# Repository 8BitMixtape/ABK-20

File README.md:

# ABK-20

**8-Bit Algorithmic Audio Synthesizer with 5×4 NeoPixel Matrix Display**

The **ABK-20** is a modernized desktop hardware console redesign of the legendary **8Bit Mixtape**. Powered by a Microchip ATtiny85 running an 8-bit algorithmic sound engine (bytebeats, wavetable, granular, and punk console synths), it features an illuminated **20-LED (5×4) visual display screen**, tactile physical controls, and instant sound sketch loading via the **AudioBoot** bootloader.

---

## Hardware Highlights

* **Microcontroller**: Microchip ATtiny85 running at 16 MHz (Internal PLL).
* **Visual Display**: **20x WS2812B / SK6812 RGB NeoPixels** arranged in a 5-column × 4-row matrix for expressive animations, meters, and UI feedback.
* **Illuminated Slide Fader**: Bourns PTL20 20mm slide potentiometer with an integrated lever LED tied to the status/data line (`PB0`).
* **Tactile Controls**:
  * **Illuminated Rotary Potentiometer**: 10kΩ vertical potentiometer (`POT2-CV1` on `PB4`, RV09 / Alpha RD901F compatible) with illuminated transparent knurled shaft.
  * **Master Volume Control**: Side-mounted thumbwheel potentiometer (`POT3-Vol1`).
  * **Navigation Switch**: MTS-102 sub-miniature toggle switch (`SW3`) on `PB3` for menu navigation and mode selection.
  * **Illuminated User Button**: Highly KS01-BL-13 round illuminated push button (`SW2`) on the `PB3` resistor ladder.
  * **Hardware Reset Button**: Dedicated tactile push button (`SW4`) pulling `PB5` (Reset) to ground.
* **Audio Circuit**:
  * High-speed 8-bit PWM audio synthesized via Timer1 64 MHz PLL.
  * On-board PAM8002 audio amplifier optimized for unity gain ($R_{14} = 22\text{k}\Omega$, $C_5 = 1\mu\text{F}$, $C_8 = 100\text{nF}$) to prevent clipping and preserve deep sub-bass bytebeats through the internal speaker.
  * 3.5mm stereo output jack (switchable line-out / headphones with volume control).
* **AudioBoot Programming**: Upload new sound sketches directly through an audio cable or web browser—no external programmer or USB serial driver required.
* **Power Circuit**:
  * **USB-C 5V Input**: Modern 6-pin USB-C receptacle (`J5`) with dual 5.1kΩ pull-down resistors (`R17`, `R18` on CC1/CC2) for universal compatibility with USB-PD smart chargers and MacBook Type-C ports.
  * **Diode OR-ing Protection**: Automatic seamless power switching via Schottky diodes (`SS14`) across USB-C (5V), 7805 DC In (7–12V), and 3x AAA Battery input with reverse-charge protection.
  * **Master Power Switch**: Latching push switch (`SW1`) with power status LED (`D-POW1`). Cycling `SW1` provides the exact power-cycle timing required to activate AudioBoot sketch loading.

---

## Schematic

The ABK-20 schematic is organized into a modular **KiCad 9 hierarchical architecture**:

### Page 1: Main Architecture & Sound Engine
Controls, ATtiny85 microcontroller, audio filtering, power regulation, and hierarchical sub-sheet block.

### Page 2: 5×4 NeoPixel Display Matrix
Dedicated hierarchical sub-sheet (`hardware/LED_Matrix.kicad_sch`) with the raster-scan daisy-chained 20-LED array.

📄 **[Download Complete Multi-Page Schematic PDF (A4)](docs/hardware/ABK-20_schematic.pdf)**

---

## PCB Layout & 3D Model View

The compact **75×80 mm** rounded-corner desktop PCB design features the centered 5×4 NeoPixel display matrix, framed by the Bourns illuminated slide fader, clear-shaft illuminated rotary potentiometer, 3-way toggle switch, tactile buttons, thumbwheel volume pot, audio jacks, and side expansion headers:

### Hardware Variants & Comparison Showroom
The repository includes a dedicated standalone showroom board ([`ABK-20_showcase_variants.kicad_pcb`](hardware/ABK-20_showcase_variants.kicad_pcb)) for mechanical verification, 3D rendering, and rapid component swapping across various hardware options:
* **Audio Jacks**: PJ-317 vertical, PJ-342 SMD gullwing, and CUI SJ1-3525N horizontal jacks.
* **Faders & Pots**: 20mm and 30mm Bourns slide pots, Alpha RD901F vertical, and 16mm back-pad pots.
* **Power & Battery**: 3x AAA on-board battery clip holders, barrel jack, and USB-C.

### Component Staging & Exploration
Earlier component staging layout used during initial mechanical fit checks, 3D VRML model validation, and footprint library curation:

---

## Frontplate & Enclosure Ecosystem

The repository provides fully parametric OpenSCAD designs and production deliverables in [`production/`](production/):

### 1. Parametric 3D-Printed Frontplate (`production/ABK20-case/`)
A dedicated OpenSCAD front panel ([`ABK-20_frontplate_3dprint.scad`](production/ABK20-case/ABK-20_frontplate_3dprint.scad)) designed for standard 16 HP ($80.96 \times 92.28\text{ mm}$) Eurorack rails or the desktop laser-cut chassis:
* **Integrated 5×4 Baffle Grid**: Extends downward to the PCB to completely isolate each NeoPixel and prevent optical light bleed between cells.
* **Selectable Matrix Styles** (via OpenSCAD Customizer):
  * **`diffuser_grid`**: Integrated $0.20\text{ mm}$ translucent 3D-printed diffuser skin (single-extruder M600 filament swap: white on bed, colored panel face).
  * **`open_frame_grid`**: Crisp open apertures with elegant top edge bevels.
  * **`window_recess`**: Stepped frame recess for an acrylic window insert.
* **Mounting & Cutouts**: M3 Eurorack mounting slots with counterbore recesses, underside PCB corner standoffs, and precise cutouts for the slide fader, pots, switches, buttons, and expansion headers.
* **Pre-Rendered STL**: [`ABK-20_frontplate_3dprint.stl`](production/ABK20-case/ABK-20_frontplate_3dprint.stl) and configuration presets in [`ABK-20_frontplate_3dprint.json`](production/ABK20-case/ABK-20_frontplate_3dprint.json).

<p align="center">
  
  &nbsp;&nbsp;&nbsp;&nbsp;
  
</p>

### 2. Laser-Cut Frontplates (`production/frontplate/`)
* **Vector Artwork Panels** ([`production/frontplate/ABK_frontplate_02.svg`](production/frontplate/ABK_frontplate_02.svg), [`output.pdf`](production/frontplate/output.pdf)): High-detail laser cutting and surface engraving artwork with silkscreen labeling and control indicators.

### 3. Parametric Enclosures (`production/ABK20-case/`)
* **3D-Printable Snap-Fit Enclosure** ([`ABK-20_case_3dprint.scad`](production/ABK20-case/ABK-20_case_3dprint.scad), [`.stl`](production/ABK20-case/ABK-20_case_3dprint.stl), [`.3mf`](production/ABK20-case/ABK-20_case_3dprint.3mf)):
  * Two-part direct-fit enclosure (`top_shell` + `bottom_cover`) designed for supportless FDM 3D printing with integrated 5×4 NeoPixel baffle grid.
  * **Prototype Hardware Support (Preset: `"perfect Proto"`)**: Specifically tailored for early prototype boards with top-mounted PJ-317 audio jacks. Adds beveled rectangular window cutouts ($14.5\times 15.5\text{ mm}$, $R=1.4\text{ mm}$) centered over each jack and widens lateral board clearance to $1.5\text{ mm}$ for effortless PCB insertion around the side thumbwheel volume pot.
  * **Standard Production (Preset: `"ABK-20_diffuser_grid"`)**: Solid continuous top face with rear-exiting audio jack ports.
* **Laser-Cut Desktop Console ("Chistli")** ([`ABK-20_case.scad`](production/ABK20-case/ABK-20_case.scad)):
  * Parametric finger-jointed desktop chassis in 3mm acrylic or wood with an ergonomic $12^\circ$ playing tilt.
  * Extended side cheeks with custom corner radii and Eurorack rail mounting options.
* **Enclosure Documentation**: [**`production/ABK20-case/README.md`**](production/ABK20-case/README.md) & [**`CASE_DESIGN_NOTES.md`**](production/ABK20-case/CASE_DESIGN_NOTES.md).

<p align="center">
  
  &nbsp;&nbsp;&nbsp;&nbsp;
  
</p>

### 4. Acoustic Optimization & Waveguide Engineering
The repository includes a comprehensive acoustic engineering architecture to solve the acoustic dipole short-circuit on rear-mounted micro-speakers and dramatically enhance bass/mid punch on physical hardware:
* **Master Engineering Plan**: [**`production/ABK20-case/ACOUSTIC_OPTIMIZATION_PLAN.md`**](production/ABK20-case/ACOUSTIC_OPTIMIZATION_PLAN.md)
  * **Downward Acoustic Chimney Waveguide**: Integrated directly into both the 3D-printed case ceiling and Eurorack faceplate. Tapers downward to seal against the PCB acoustic holes, transforming the $8.1\text{ mm}$ airspace into an acoustic horn with $+3\text{ to }+6\text{ dB}$ higher acoustic projection and zero internal sound spill.
  * **8 Classic Vintage Sound Grill Styles** (selectable via `speaker_grill_style`):
    * **`horiz_slots`**: Classic Dieter Rams / Braun T3 tiered horizontal slits.
    * **`horiz_4slots`**: 4 thin horizontal slits (retro 70s/80s Hi-Fi cassette deck).
    * **`soundwave`**: 7 graduated vertical slits forming an analog synth graphic EQ waveform.
    * **`braun_dots`**: 19-hole staggered precision dot matrix (Braun ET66 / T41).
    * **`chevron`**: $45^\circ$ angled Japanese synth louvers (Roland TR/TB style).
    * **`radial`**: 1950s transistor radio radial dial spoke starburst.
    * **`slots`**: Classic 5 vertical Eurorack slots.
    * **`aperture`**: Open framed window for real speaker cloth or brass wire mesh.
  * **Modular Acoustic Kit** ([`production/ABK20-case/ABK-20_speaker_acoustic_kit.scad`](production/ABK20-case/ABK-20_speaker_acoustic_kit.scad)):
    * Parametric sealed and Helmholtz bass-reflex back-box cups (Standard $2.4\text{ cm}^3$, XL $5.1\text{ cm}^3$, and MAX $6.3\text{ cm}^3$) with extended snorkel ducts tuned to $280-360\text{ Hz}$.
    * **Support-Free Printing**: Continuous flat PCB support keel at $Z = \text{depth}$ with $\le 45^\circ$ transitional chamfers prints 100% support-free when oriented flange-down.
  * **Precision Centering**: Added `panel_alignment = "symmetric"` to resolve legacy SVG viewBox offsets, achieving exact $2.98\text{ mm}$ symmetrical PCB margins and balanced top jack outer walls.

---

## ATtiny85 Pin Mapping

| Pin | Physical | Port | Macro | Function / Description |
| :---: | :---: | :---: | :---: | :--- |
| **PB0** | Pin 5 | `PB0` | `NEOPIXELPIN` | 800 kHz data stream to 5×4 NeoPixel Matrix (via R9 330Ω) & Fader Lever LED (`RV1B`) |
| **PB1** | Pin 6 | `PB1` | `SPEAKERPIN` | High-speed PWM audio output (Timer1 64 MHz PLL) to Volume Pot & PAM8002 amp |
| **PB2** | Pin 7 | `PB2` | `POTI_LEFT` | Slide Potentiometer (`RV1A`) analog control input (ADC1) |
| **PB3** | Pin 2 | `PB3` | `BUTTON_PIN` | AudioBoot audio input (AC-coupled 100nF) & multi-state button resistor ladder (ADC3) |
| **PB4** | Pin 3 | `PB4` | `POTI_RIGHT` | 10kΩ Rotary Potentiometer (`POT2-CV1`) analog control input (ADC2) |
| **PB5** | Pin 1 | `PB5` | `RESET_PIN` | Hardware Reset button (`SW4`) & Sync jumper (`J6`). *(Can be converted to MIDI IN with `RSTDISBL`)* |

---

## Firmware & Web Flasher

* **[ABK-20 Online Web Audio Player & Flasher](https://8bitmixtape.github.io/ABK-20/)** (hosted directly from [`web/index.html`](web/index.html))
* **[Software & Sketches Suite](software/)** (PlatformIO build environment, `hex2wav` pipeline, and 30+ sound sketches)
* Also compatible with the [8Bit-Vintage Firmware Repository](https://github.com/8BitMixtape/8Bit-Vintage)

---

## TinyAudioBoot Bootloader (ABK-20 Custom Edition)

The ABK-20 features a dedicated, highly optimized build of **TinyAudioBoot** for ATtiny85 running at 16 MHz internal PLL, fully documented in [**`software/tools/bootloader/`**](software/tools/bootloader/):

* **Skipper Edition** ([`TinyAudioBoot_Skipper_ABK-20.hex`](software/tools/bootloader/hex/TinyAudioBoot_Skipper_ABK-20.hex), 960 bytes):
  * **Instant Boot**: Starts the active synthesizer sketch in $< 25\text{ ms}$ upon normal power-on.
  * **Upload Mode on Demand**: Enters a 30-second audio upload window *only* when holding button **`SW2`** during power-up or reset.
* **Standard Edition** ([`TinyAudioBoot_Standard_ABK-20.hex`](software/tools/bootloader/hex/TinyAudioBoot_Standard_ABK-20.hex), 874 bytes):
  * Provides an automatic 5-second audio upload window on every power cycle.
* **Silent Standby on PB1**:
  * Actively clamps `PB1` to GND during bootloader standby so there are zero pops, clicks, or 1 Hz ticking chirps in headphones or speaker.
* **Page-Write Bi-Color Visuals**:
  * Alternates **Green $\leftrightarrow$ Red** on every 64-byte flash page write for real-time visual progress monitoring.
* **Flash Budget**:
  * Occupies $\le 1\text{ KB}$ at address `0x1C00`, maximizing flash memory to **7,168 bytes** ($0\text{x0000} \to 0\text{x1BFF}$) for user sketches.
* **ISP Flashing & Fuses**:
  * Quick one-liner AVRDUDE flash commands and fuse reference (`lfuse: 0xe1`, `hfuse: 0xdd`, `efuse: 0xfe`) are detailed in [**`software/tools/bootloader/burn_bootloader.md`**](software/tools/bootloader/burn_bootloader.md).
* **Architecture & Evolution**:
  * Comprehensive breakdown of all circuit and firmware differences compared to the original v3.0–v3.2 bootloader in [**`software/tools/bootloader/BOOTLOADER_EVOLUTION_AND_DIFFERENCES.md`**](software/tools/bootloader/BOOTLOADER_EVOLUTION_AND_DIFFERENCES.md).

---

## Repository Structure

```
ABK-20/
├── .agents/                          # Antigravity agent rules & 8Bit Mixtape skills
├── web/                              # Web AudioBoot player & sound app catalog (GitHub Pages)
│   ├── index.html                    # Online Web Audio Flasher & synthesizer player
│   ├── apps.json & apps.js           # Sound track catalog metadata & registry
│   ├── wav/                          # Production 8-bit bootloader audio streams (.wav)
│   ├── audio/                        # 30-second audio preview MP3s
│   ├── gifs/                         # Animated 5x4 matrix LED previews (solid clean mode)
│   └── manuals/                      # Individual user manuals for each sound application
├── docs/                             # Project documentation, hardware notes & datasheets
│   ├── hardware/                     # Circuit notes, engineering summaries & schematics
│   │   ├── HARDWARE_NOTES.md         # Hardware & circuit design notes
│   │   ├── REV03_ENGINEERING_SUMMARY.md # Engineering breakdown
│   │   ├── AMP_AUTO_SHUTDOWN_CIRCUIT.md # LM4871 amp shutoff specification
│   │   ├── DESIGN_VARIANTS_GUIDE.md  # Alternative layout variants
│   │   └── ABK-20_schematic.pdf      # Multi-page A4 schematic export
│   ├── datasheets/                   # Component datasheets (Bourns faders, switches, pots)
│   ├── fabrication/                  # DIY etching & drilling guides (ABK-20_DIY_DRILL_HANDOUT.pdf)
│   ├── history/                      # 8Bit Mixtape lineage & Coconut doctrine (HISTORY_AND_ARCHITECTURE.md)
│   ├── software/                     # Software developer guides (WORKFLOW_GIF_GENERATION.md)
│   └── img/                          # Images, 3D renders & diagrams
├── hardware/                         # KiCad 8 EDA design source files
│   ├── ABK-20.kicad_pro              # Factory Project: KiCad project file
│   ├── ABK-20.kicad_sch              # Factory Project: Main hierarchical schematic (Page 1)
│   ├── ABK-20.kicad_pcb              # Factory Project: Board layout (JLCPCB / PTH / SMT)
│   ├── ABK-20_DIY.kicad_pro          # DIY Project: KiCad project file
│   ├── ABK-20_DIY.kicad_sch          # DIY Project: Dedicated schematic (Page 1)
│   ├── ABK-20_DIY.kicad_pcb          # DIY Project: Board layout (non-PTH / wire-vias / pilot marks)
│   ├── ABK-20_showcase_variants.*    # Standalone showroom project with alternative footprints
│   ├── LED_Matrix.kicad_sch          # 5x4 NeoPixel matrix sub-sheet (Page 2)
│   ├── mixtape_schematics.kicad_sym  # Project symbol library
│   ├── 8Bitmixtape_reworked.pretty/  # Project footprint library
│   ├── 3d_models/                    # Self-contained bundled 3D models
│   ├── bom/                          # Hardware schematic BOM exports
│   └── scripts/                      # Layout, 3D WRL & thumbnail scripts
├── production/                       # Physical manufacturing & fabrication deliverables
│   ├── bom/                          # Interactive HTML Bill of Materials (iBOM)
│   ├── gerbers/                      # Standard fabrication drill & Gerber archives
│   ├── MASK/                         # High-res vector masks for DIY PCB chemical etching
│   ├── frontplate/                   # Laser-cut / CNC front panel vector drawings (SVG)
│   └── ABK20-case/                   # 3D printable enclosures and mechanical drawings
└── software/                         # Embedded C++ firmware, tools & asset pipelines
    ├── platformio.ini                # PlatformIO ATtiny85 @ 16 MHz build configuration
    ├── src/                          # 30+ algorithmic sound sketches (.cpp)
    ├── include/                      # Hardware pinouts & shared sound engine headers (.h)
    ├── scripts/                      # Asset pipelines (build_wavs, gen_previews, gen_audio_previews)
    └── tools/
        ├── bootloader/               # TinyAudioBoot sources, Makefile & precompiled HEX binaries
        └── hex2wav/                  # Standalone Hex-to-Audio bootloader converter
```

---

## License

Licensed under the **[CERN Open Hardware Licence Version 2 – Strongly Reciprocal](LICENSE)** (CERN-OHL-S-2.0).

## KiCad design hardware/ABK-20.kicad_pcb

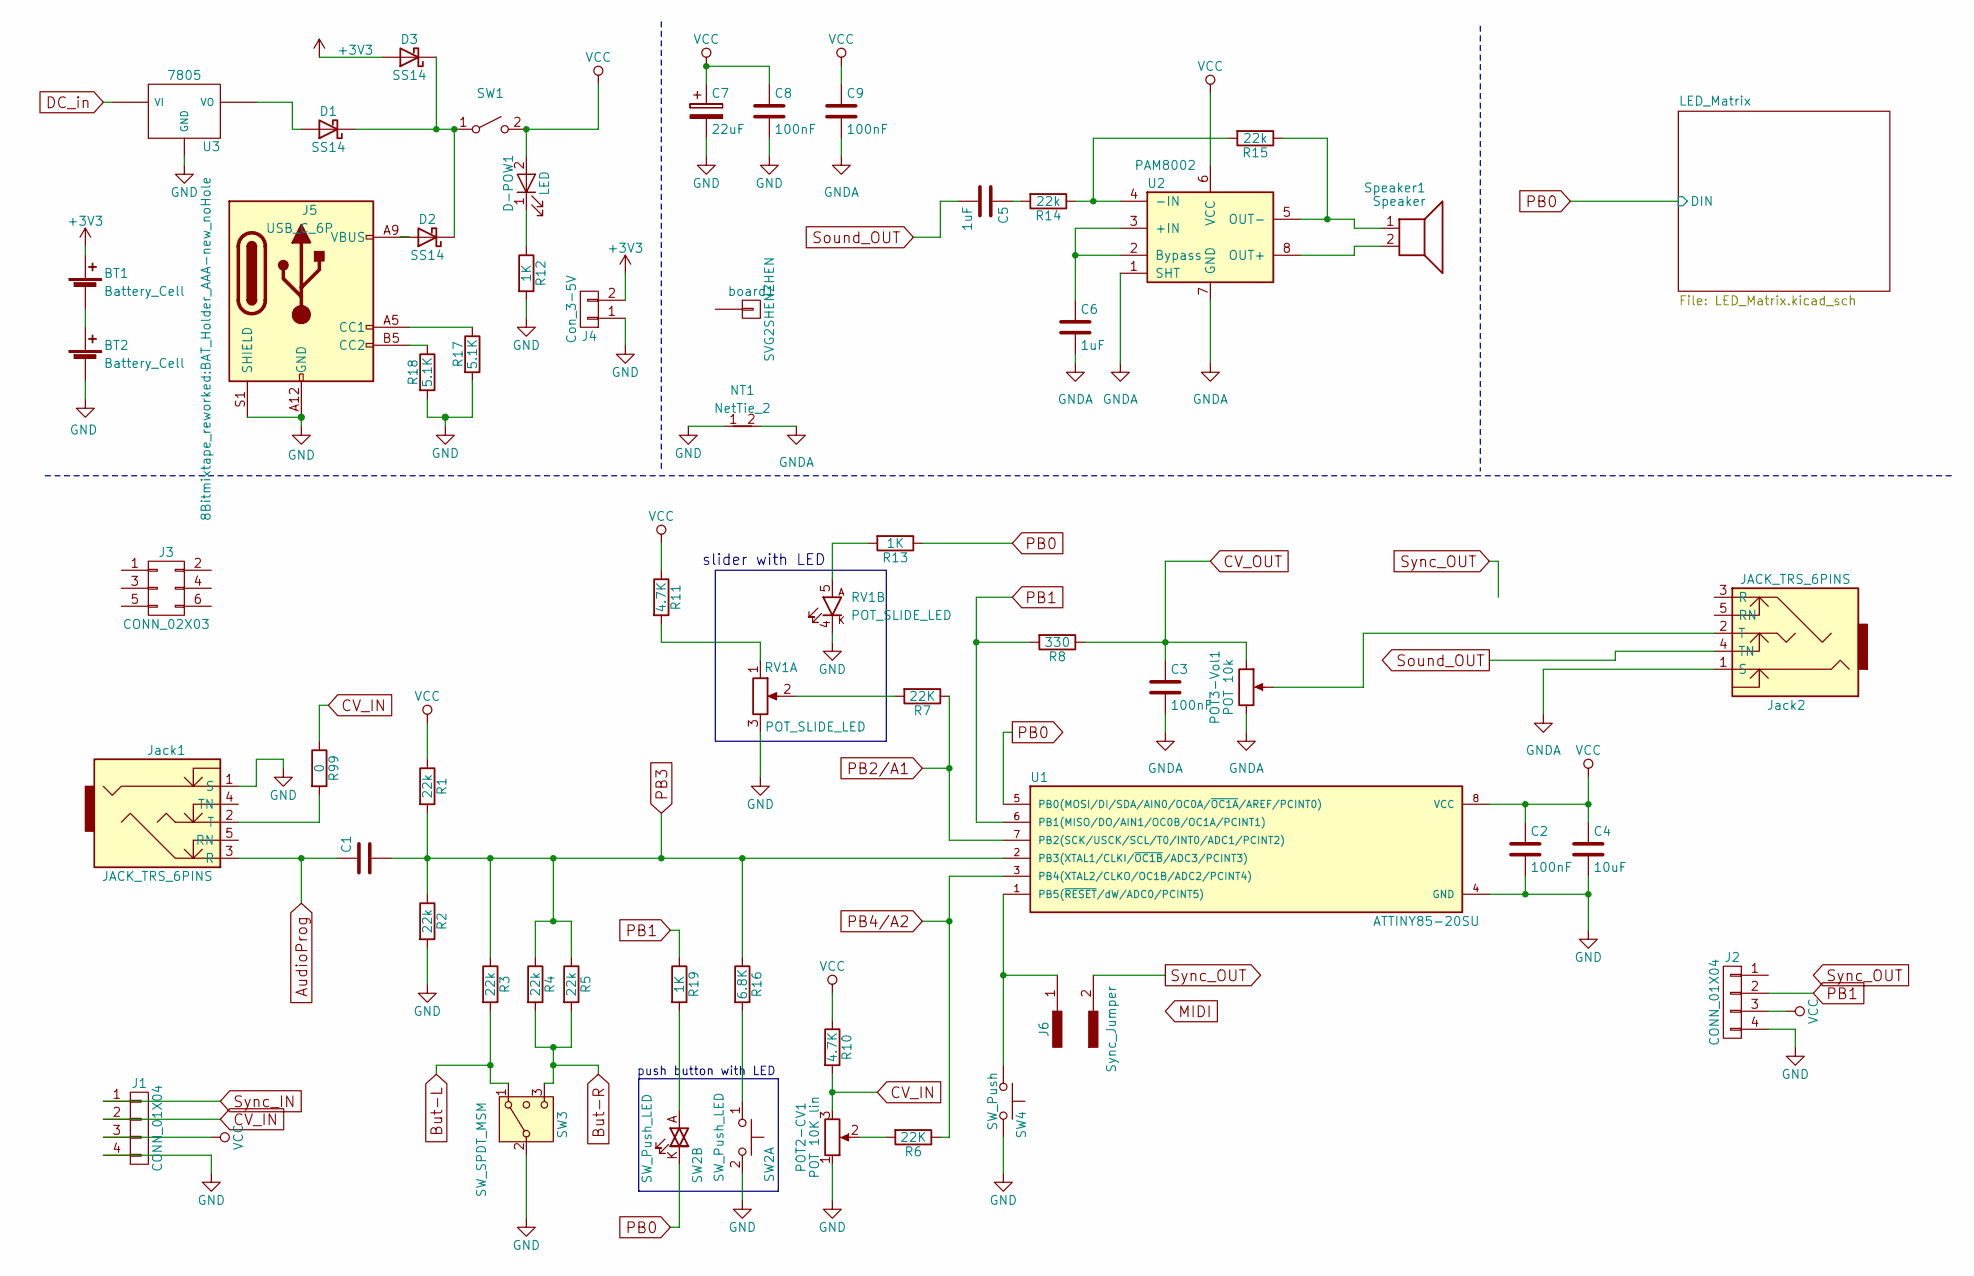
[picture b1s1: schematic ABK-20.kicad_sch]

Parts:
BT1, BT2: Battery_Cell; BAT_Holder_AAA-new_noHole
C1, C2, C3, C8, C9: 100nF; C_1210_noGND
C4: 10uF; C_1210_noGND
C5, C6: 1uF; C_1210_noGND
C7: 22uF; C_1210_noGND
D1, D2, D3: SS14; D_SMA
D-POW1: LED; LED_2835_minimal
J1: CONN_01X04; Angled_1x04_Pitch2.54mm-flip
J2: CONN_01X04; PinSocket_1x04_P2.54mm_Vertical
J3: CONN_02X03; Socket_Strip_Straight_2x03_Pitch2.54mm
J4: Con_3-5V; Bat_connector_SMD
J5: USB_C_6P; USB_C_6Pin_PowerOnly
J6: Sync_Jumper; Sync_jumper_small
Jack1, Jack2: JACK_TRS_6PINS; AUDIO-Jack_3.5mm_PJ-317
NT1: NetTie_2; NetTie-2_SMD_Pad2.0mm
POT2-CV1: POT 10K lin; Potentiometer_RV09_Vertical_ClearShaft
POT3-Vol1: POT 10k; Potentiometer_wheel
R1, R2, R3, R4, R5, R14, R15: 22k; R_1206_noGND_sm
R6, R7: 22K; R_1206_noGND_sm
R8: 330; R_1206_noGND_sm
R10, R11: 4.7K; R_1206_noGND_sm
R12, R13, R19: 1K; R_1206_noGND_sm
R16: 6.8K; R_1206_noGND_sm
R17, R18: 5.1K; R_1206_noGND_sm
R99: 0; R_1206_noGND_sm
RV1: POT_SLIDE_LED; Potentiometer_Bourns_PTL20_Single_Slide_LED
SW1: SW_SPST; Push_SWITCH_hole
SW2: SW_Push_LED; SW_Push_Highly_KS01-BL-13
SW3: SW_SPDT_MSM; SW_Toggle_SPDT_SubMini_SMTS-103
SW4: SW_Push; SW_SPST_FSMSM
Speaker1: Speaker; SpeakerPads_SMD
U1: ATTINY85-20SU; Attiny_DIP-8_W7.62mm_mod
U2: PAM8002; SO-8_fixed
U3: 7805; TO-252-3_TabPin2
board1: SVG2SHENZHEN; Mixtape_reworked

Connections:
+3V3: BT1.1 (+), D3.2 (A), J4.2
AudioProg: C1.1, Jack1.3 (R)
But-L: R3.2, SW3.1
But-R: R4.2, R5.2, SW3.3 (4)
CV_IN: J1.2, POT2-CV1.3, R10.2, R99.1
CV_OUT: C3.1, POT3-Vol1.1, R8.1
DC_in: U3.1 (VI)
GND: BT2.2 (-), C2.2, C4.2, C7.2, C8.2, J1.4, J2.4, J4.1, J5.A12 (GND), J5.B12 (GND), J5.S1 (SHIELD), Jack1.1 (S), NT1.1, POT2-CV1.1, R2.2, R12.2, R17.2, R18.2, RV1.3, RV1.4 (K), SW2.2, SW3.2 (3), SW4.2, U1.4 (GND), U3.2 (GND); also elsewhere on the board
GNDA: C3.2, C6.2, C9.2, Jack2.1 (S), NT1.2, POT3-Vol1.3, U2.1 (SHT), U2.7 (GND)
unnamed: BT1.2 (-), BT2.1 (+)
unnamed: C5.1, R14.2
unnamed: D1.2 (A), U3.3 (VO)
unnamed: D1.1 (K), D2.1 (K), D3.1 (K), SW1.1 (A)
unnamed: D2.2 (A), J5.A9 (VBUS), J5.B9 (VBUS)
unnamed: D-POW1.1 (K), R12.1
unnamed: J5.A5 (CC1), R17.1
unnamed: J5.B5 (CC2), R18.1
unnamed: Jack1.2 (T), R99.2
unnamed: Jack2.2 (T), POT3-Vol1.2
unnamed: POT2-CV1.2, R6.2
unnamed: R7.2, RV1.2
unnamed: R11.2, RV1.1
unnamed: R16.2, SW2.1
unnamed: R19.2, SW2.A
unnamed: R13.2, RV1.5 (A)
unnamed: J6.1, SW4.1, U1.1 (PB5(~RESET/dW/ADC0/PCINT5))
unnamed: C6.1, U2.2 (Bypass), U2.3 (+IN)
unnamed: R14.1, R15.2, U2.4 (-IN)
unnamed: Speaker1.2, U2.8 (OUT+)
unnamed: R15.1, Speaker1.1, U2.5 (OUT-)
PB0: R13.1, SW2.K, U1.5 (PB0(MOSI/DI/SDA/AIN0/OC0A/~OC1A/AREF/PC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); also elsewhere on the board
PB1: J2.2, R8.2, R19.1, U1.6 (PB1(MISO/DO/AIN1/OC0B/OC1A/PCINT1))
PB2/A1: R7.1, U1.7 (PB2(SCK/USCK/SCL/T0/INT0/ADC1/PCINT2))
PB3: C1.2, R1.2, R2.1, R3.1, R4.1, R5.1, R16.1, U1.2 (PB3(XTAL1/CLKI/~OC1B/ADC3/PCINT3))
PB4/A2: R6.1, U1.3 (PB4(XTAL2/CLKO/OC1B/ADC2/PCINT4))
Sound_OUT: C5.2, Jack2.4 (TN)
Sync_IN: J1.1
Sync_OUT: J6.2
VCC: C2.1, C4.1, C7.1, C8.1, C9.1, D-POW1.2 (A), J1.3, J2.3, R1.1, R10.1, R11.1, SW1.2 (B), U1.8 (VCC), U2.6 (VCC); also elsewhere on the board

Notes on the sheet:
slider with LED
push button with LED

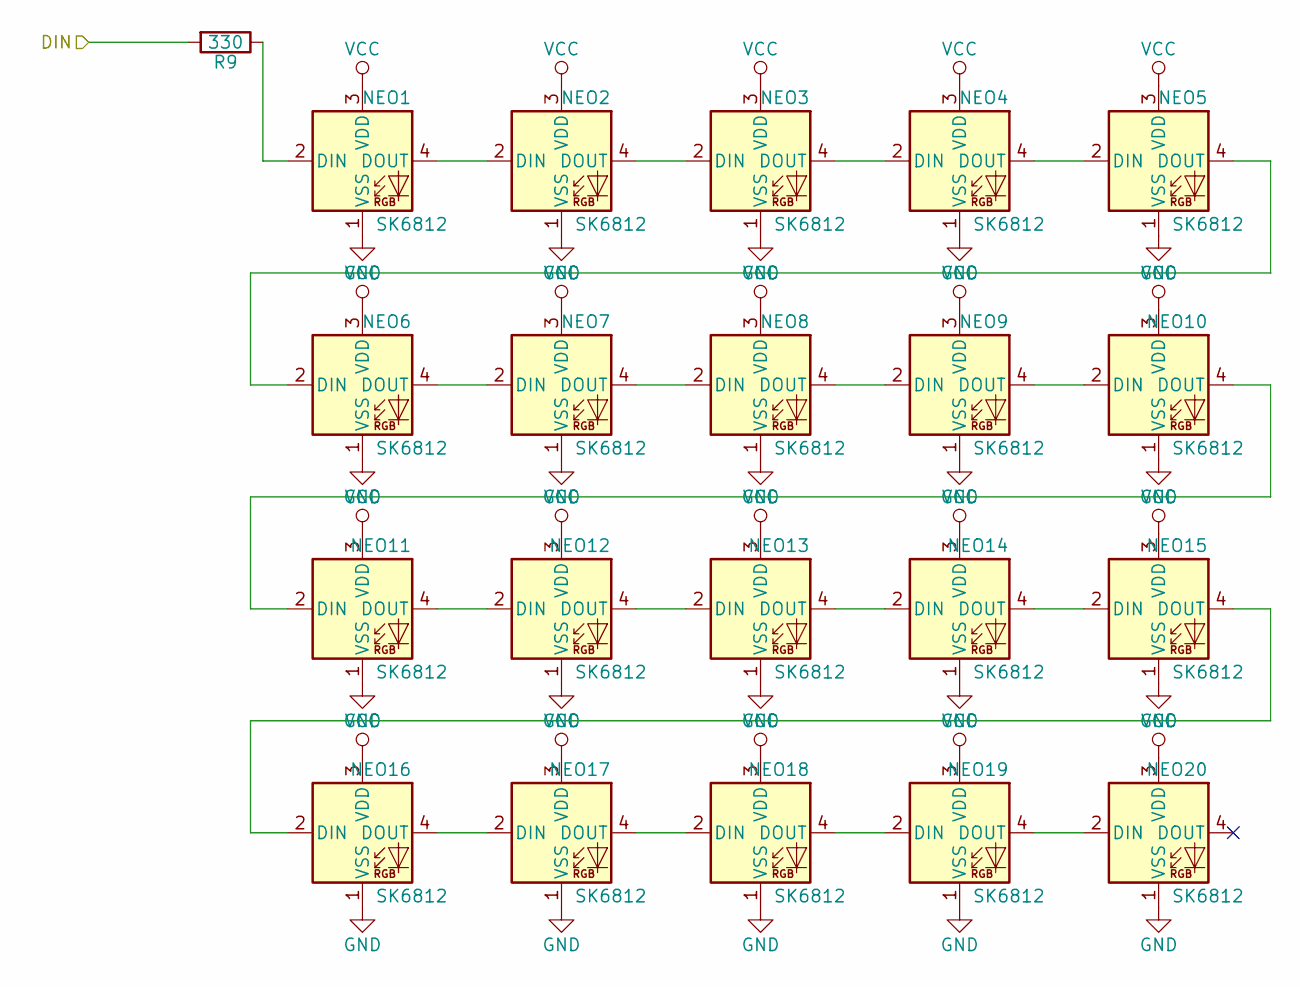
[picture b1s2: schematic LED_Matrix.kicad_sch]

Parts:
NEO1, NEO2, NEO3, NEO4, NEO5, NEO6, NEO7, NEO8, NEO9, NEO10, NEO11, NEO12, NEO13, NEO14, NEO15, NEO16, NEO17, NEO18, NEO19, NEO20: SK6812; Mixtape_NEO_WS2812B
R9: 330; R_1206_noGND_sm

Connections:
GND: NEO1.1 (VSS), NEO2.1 (VSS), NEO3.1 (VSS), NEO4.1 (VSS), NEO5.1 (VSS), NEO6.1 (VSS), NEO7.1 (VSS), NEO8.1 (VSS), NEO9.1 (VSS), NEO10.1 (VSS), NEO11.1 (VSS), NEO12.1 (VSS), NEO13.1 (VSS), NEO14.1 (VSS), NEO15.1 (VSS), NEO16.1 (VSS), NEO17.1 (VSS), NEO18.1 (VSS), NEO19.1 (VSS), NEO20.1 (VSS); also elsewhere on the board
unnamed: NEO1.2 (DIN), R9.1
unnamed: NEO1.4 (DOUT), NEO2.2 (DIN)
unnamed: NEO2.4 (DOUT), NEO3.2 (DIN)
unnamed: NEO3.4 (DOUT), NEO4.2 (DIN)
unnamed: NEO4.4 (DOUT), NEO5.2 (DIN)
unnamed: NEO5.4 (DOUT), NEO6.2 (DIN)
unnamed: NEO6.4 (DOUT), NEO7.2 (DIN)
unnamed: NEO7.4 (DOUT), NEO8.2 (DIN)
unnamed: NEO8.4 (DOUT), NEO9.2 (DIN)
unnamed: NEO9.4 (DOUT), NEO10.2 (DIN)
unnamed: NEO10.4 (DOUT), NEO11.2 (DIN)
unnamed: NEO11.4 (DOUT), NEO12.2 (DIN)
unnamed: NEO12.4 (DOUT), NEO13.2 (DIN)
unnamed: NEO13.4 (DOUT), NEO14.2 (DIN)
unnamed: NEO14.4 (DOUT), NEO15.2 (DIN)
unnamed: NEO15.4 (DOUT), NEO16.2 (DIN)
unnamed: NEO16.4 (DOUT), NEO17.2 (DIN)
unnamed: NEO17.4 (DOUT), NEO18.2 (DIN)
unnamed: NEO18.4 (DOUT), NEO19.2 (DIN)
unnamed: NEO19.4 (DOUT), NEO20.2 (DIN)
PB0: R9.2; also elsewhere on the board
VCC: NEO1.3 (VDD), NEO2.3 (VDD), NEO3.3 (VDD), NEO4.3 (VDD), NEO5.3 (VDD), NEO6.3 (VDD), NEO7.3 (VDD), NEO8.3 (VDD), NEO9.3 (VDD), NEO10.3 (VDD), NEO11.3 (VDD), NEO12.3 (VDD), NEO13.3 (VDD), NEO14.3 (VDD), NEO15.3 (VDD), NEO16.3 (VDD), NEO17.3 (VDD), NEO18.3 (VDD), NEO19.3 (VDD), NEO20.3 (VDD); also elsewhere on the board

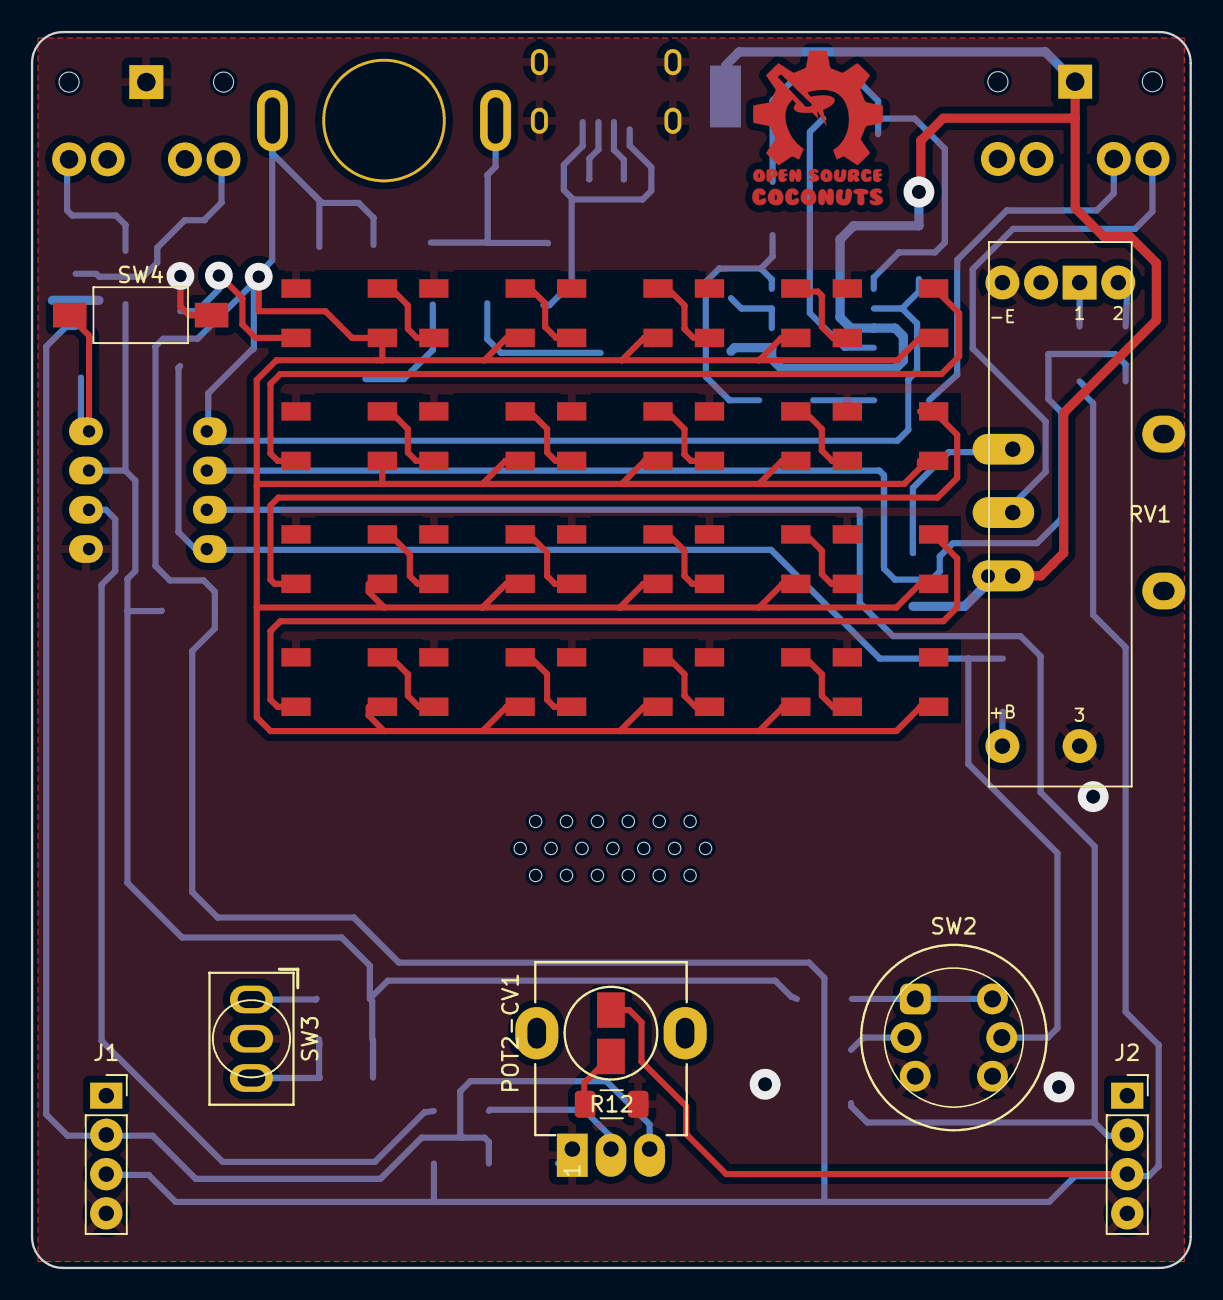
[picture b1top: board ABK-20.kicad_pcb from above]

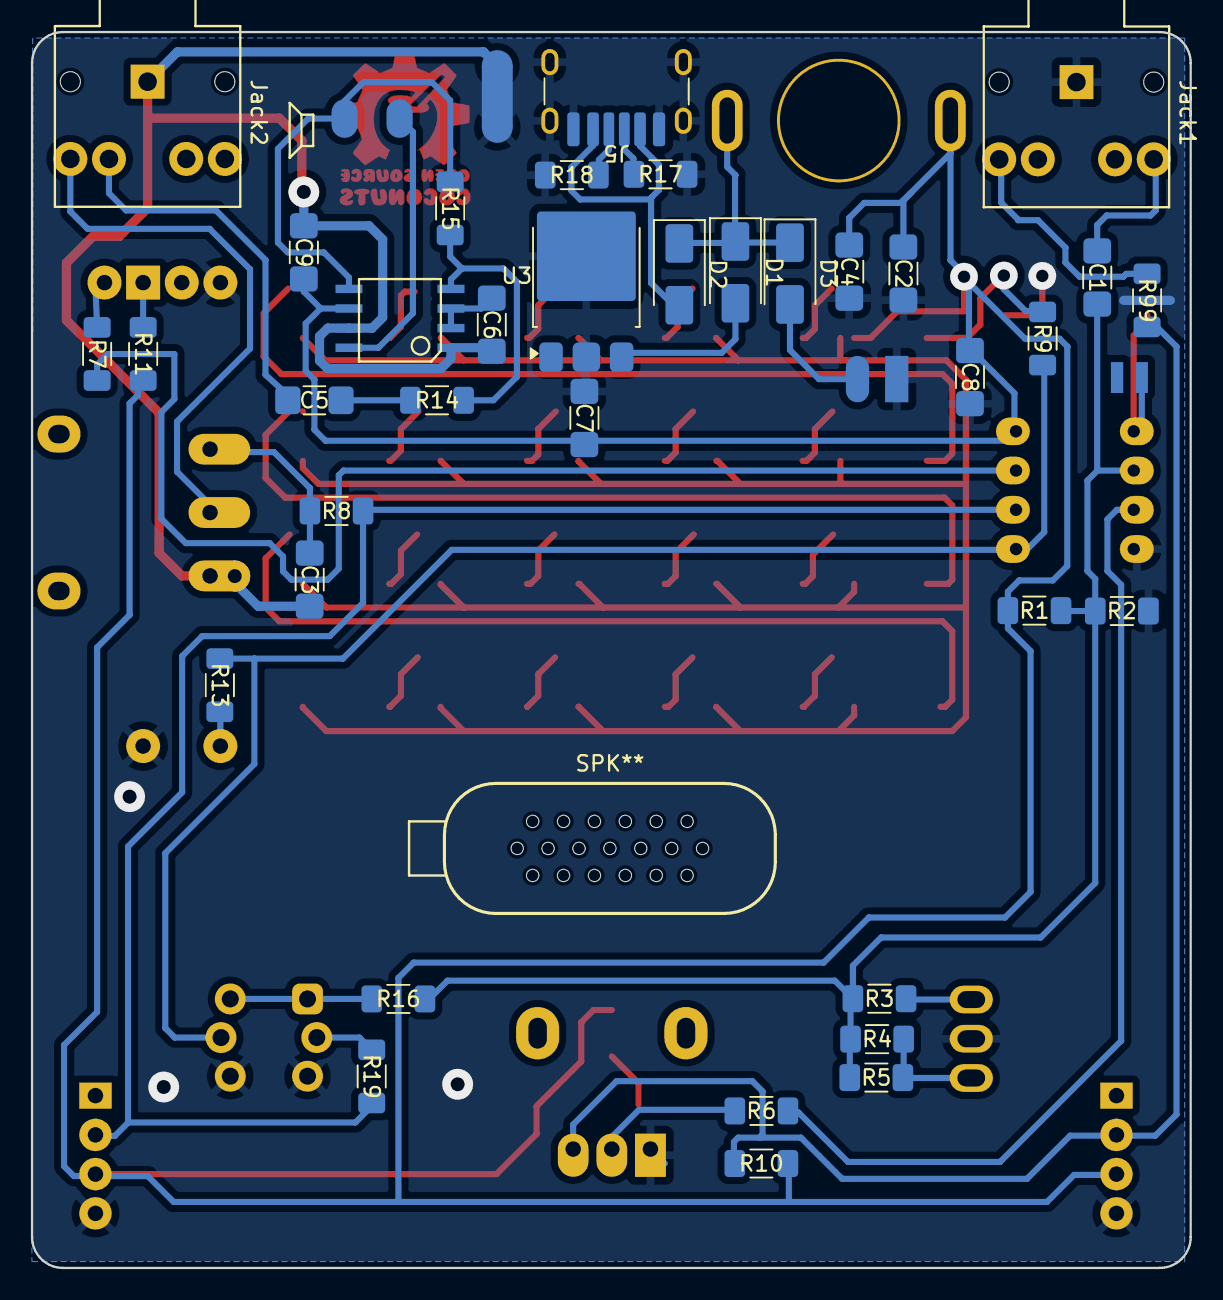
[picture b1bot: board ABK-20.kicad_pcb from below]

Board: 2 copper layers, 75.0 x 80.0 mm, 74 parts (42 on the bottom side), 55 nets.

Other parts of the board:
Ref**: Val**; Coconut_logo_sm
SPK**: Speaker_Micro_Loch_Honeycomb

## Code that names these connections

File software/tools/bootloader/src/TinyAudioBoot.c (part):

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  v3.1  04.2.2017 C. -H-A-B-E-R-E-R-  clean reset vector added, description added, pins rerouted
  v3.2  18.7.2017 C. -P-r-a-k-o-s-a-  various refactor, added eeprom write mode, makefile for compiling using arduino ide toolchain
  v3.3  25.10.2026 M. -D-U-S-S-E-I-L-L-E-R- (dusjagr) & Antigravity
                   - Silent speaker standby: PB1 held at GND (0V) while PB0 blinks Red @ 1 Hz
                   - Alternating Green <-> Red bi-color LED visual feedback on each 64-byte page
                   - Code size optimizations (pgm_read_word, inline delay loops) down to 872 bytes
                   - Standard 1KB boundary at 0x1C00 (leaves 7,168 bytes flash for user sketches)
                   - Configurable upload timeout: 5s for Standard, 30s for Skipper
  v4.0  25.10.2026 M. -D-U-S-S-E-I-L-L-E-R- (dusjagr) & Antigravity - ABK-20 Skipper Edition
                   - Instant boot: skips bootloader in <25ms unless button SW2 is held on power-up
                   - PB3 analog resistor ladder ADC decoder (calibrated threshold ADCH <= 60 / < 1.18V)
                   - ADC-based button release wait and 20ms debounce (prevents chatter lockups)
                   - Unified single-source architecture controlled via -DUSE_SKIPPER (958 bytes)

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				
	   			     _______
                                    |   U   |
         (PCINT5/RESET/ADC0/dW) PB5-|       |- VCC
  (PCINT3/XTAL1/CLKI/OC1B/ADC3) PB3-| ATTINY|- PB2 (SCK/USCK/SCL/ADC1/T0/INT0/PCINT2) 
  (PCINT4/XTAL2/CLKO/OC1B/ADC2) PB4-|   85  |- PB1 (MISO/DO/AIN1/OC0B/OC1A/PCINT1) 
                                GND-|       |- PB0 (MOSI/DI/SDA/AIN0/OC0A/OC1A/AREF/PCINT0)	 
                                    |_______|

				  
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				  ==============
                                     _______				  
                                    |   U   |				  
                          reset/PB5-|       |- VCC				  
                 D3/A3          PB3-| ATTINY|- PB2       D2/A1				  
    soundprog->  D4/A2          PB4-|   85  |- PB1       D1     -> ARDUINO_LED
                                GND-|       |- PB0       D0
                                    |_______|		


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
#ifdef DEBUGON

	#define DEBUGPIN       ( 1<<PB2 ) 
	#define INITDEBUGPIN   { DDRB  |=  DEBUGPIN; }

	#define DEBUGPINON     { PORTB |=  DEBUGPIN;}
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#ifdef USELED

#define INITLED do { \
    DDRB |= (1 << PB0) | (1 << PB1); \
    PORTB &= ~((1 << PB0) | (1 << PB1)); \
} while(0)

#define LED_GREEN()    do { PORTB = (PORTB & ~(1 << PB0)) | (1 << PB1); } while(0)
#define LED_RED()      do { PORTB = (PORTB & ~(1 << PB1)) | (1 << PB0); } while(0)
#define LED_OFF()      do { PORTB &= ~((1 << PB0) | (1 << PB1)); } while(0)
#define TOGGLE_GREEN() do { PORTB &= ~(1 << PB0); PORTB ^= (1 << PB1); } while(0)
#define TOGGLE_RED()   do { PORTB &= ~(1 << PB1); PORTB ^= (1 << PB0); } while(0)

#define LEDON      LED_RED()
#define LEDOFF     LED_OFF()
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
#endif

#define INPUTAUDIOPIN (1<<PB3) //
#define PINVALUE (PINB&INPUTAUDIOPIN)
#define INITAUDIOPORT {DDRB&=~INPUTAUDIOPIN;} // audio pin is input

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}

#ifdef USE_SKIPPER
// Skipper button check on PB3 analog ladder
static inline void checkBootloaderSkip(void)
{
  // Power settling delay (~20ms @ 16MHz) for VCC rail and 100nF C1 capacitor
  _delay_ms(20);

  // ADC3 on PB3, VCC reference, Left-adjust result (8-bit reading in ADCH)
  ADMUX = (1 << ADLAR) | (1 << MUX1) | (1 << MUX0);
  // Enable ADC, start first warm-up conversion, prescaler 64 (~250kHz @ 16MHz)
  ADCSRA = (1 << ADEN) | (1 << ADSC) | (1 << ADPS2) | (1 << ADPS1);
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    while (ADCSRA & (1 << ADSC));
  } while (ADCH <= 60);

  // Button released: debounce delay (~20ms @ 16MHz) to let PB3 ladder settle cleanly
  _delay_ms(20);

  ADCSRA = 0; // disable ADC to save power & restore PB3 for audio
}
#endif

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

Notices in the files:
software/tools/bootloader/src/TinyAudioBoot.c:
This program is free software; you can redistribute it and/or modify
it under the terms of the GNU General Public License as published by
the Free Software Foundation; either version 2 of the License, or
(at your option) any later version.
